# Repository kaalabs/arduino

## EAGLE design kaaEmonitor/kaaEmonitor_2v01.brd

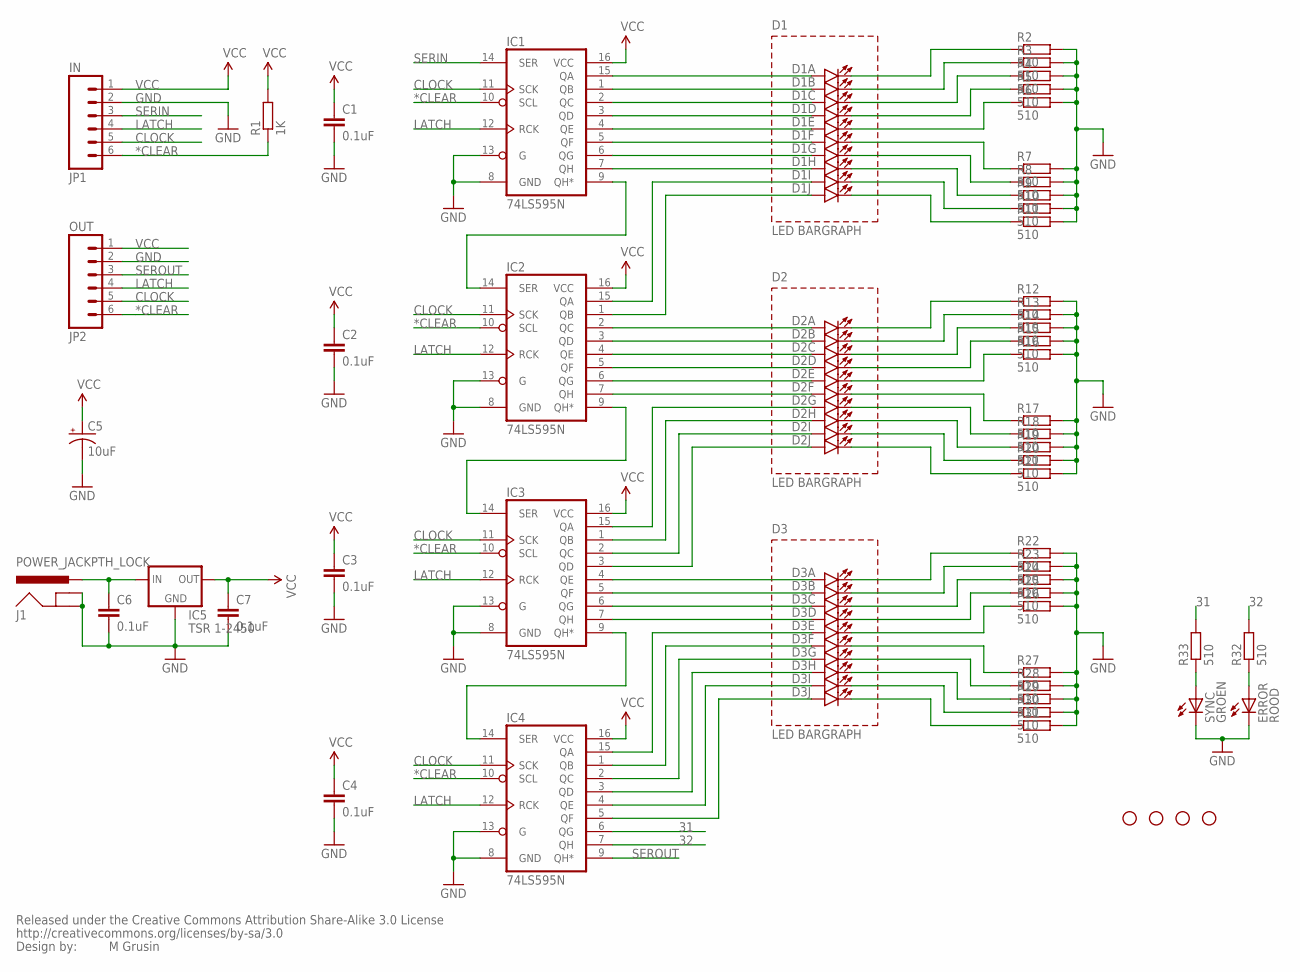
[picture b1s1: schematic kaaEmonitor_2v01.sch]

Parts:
C1, C2, C3, C4, C6, C7: 0.1uF; CAP-PTH-SMALL2
C5: 10uF; CPOL-RADIAL-10UF-25V
D1, D2, D3: LED_BARGRAPH_10; LED_BARGAPH_10
ERROR: ROOD; LED3MM
IC1, IC2, IC3, IC4: 74LS595N; DIL16
IC5: TSR 1-2450; TO220-IGO
J1: POWER_JACKPTH_LOCK; POWER_JACK_PTH_LOCK
JP1: IN; 1X06
JP2: OUT; 1X06
R1: 1K; 0204/5
R2, R3, R4, R5, R6, R7, R8, R9, R10, R11, R12, R13, R14, R15, R16, R17, R18, R19, R20, R21, R22, R23, R24, R25, R26, R27, R28, R29, R30, R31, R32, R33: 510; 0204/5
SO1, SO2, SO3, SO4: STAND-OFF
SYNC: GROEN; LED3MM
U$6: CREATIVE_COMMONS

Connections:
31: IC4.6 (QG), R33.2
32: IC4.7 (QH), R32.2
*CLEAR: IC1.10 (SCL), IC2.10 (SCL), IC3.10 (SCL), IC4.10 (SCL), JP1.6, JP2.6, R1.1
CLOCK: IC1.11 (SCK), IC2.11 (SCK), IC3.11 (SCK), IC4.11 (SCK), JP1.5, JP2.5
GND: C1.2, C2.2, C3.2, C4.2, C5.2 (-), C6.2, C7.2, ERROR.K (C), IC1.8 (GND), IC1.13 (G), IC2.8 (GND), IC2.13 (G), IC3.8 (GND), IC3.13 (G), IC4.8 (GND), IC4.13 (G), IC5.GND, J1.GND, J1.GNDBREAK, JP1.2, JP2.2, R2.2, R3.2, R4.2, R5.2, R6.2, R7.2, R8.2, R9.2, R10.2, R11.2, R12.2, R13.2, R14.2, R15.2, R16.2, R17.2, R18.2, R19.2, R20.2, R21.2, R22.2, R23.2, R24.2, R25.2, R26.2, R27.2, R28.2, R29.2, R30.2, R31.2, SYNC.K (C)
LATCH: IC1.12 (RCK), IC2.12 (RCK), IC3.12 (RCK), IC4.12 (RCK), JP1.4, JP2.4
unnamed: D1.1 (A), IC1.15 (QA)
unnamed: D1.2 (A), IC1.1 (QB)
unnamed: D1.3 (A), IC1.2 (QC)
unnamed: D1.4 (A), IC1.3 (QD)
unnamed: D1.5 (A), IC1.4 (QE)
unnamed: D1.6 (A), IC1.5 (QF)
unnamed: D1.7 (A), IC1.6 (QG)
unnamed: D1.8 (A), IC1.7 (QH)
unnamed: D1.9 (A), IC2.15 (QA)
unnamed: D1.10 (A), IC2.1 (QB)
unnamed: D2.8 (A), IC3.1 (QB)
unnamed: D2.7 (A), IC3.15 (QA)
unnamed: D2.9 (A), IC3.2 (QC)
unnamed: D2.10 (A), IC3.3 (QD)
unnamed: D3.1 (A), IC3.4 (QE)
unnamed: D3.2 (A), IC3.5 (QF)
unnamed: D3.3 (A), IC3.6 (QG)
unnamed: D3.4 (A), IC3.7 (QH)
unnamed: D2.1 (A), IC2.2 (QC)
unnamed: D2.2 (A), IC2.3 (QD)
unnamed: D2.3 (A), IC2.4 (QE)
unnamed: D2.4 (A), IC2.5 (QF)
unnamed: D2.5 (A), IC2.6 (QG)
unnamed: D2.6 (A), IC2.7 (QH)
unnamed: D1.20 (C), R2.1
unnamed: D1.19 (C), R3.1
unnamed: D3.5 (A), IC4.15 (QA)
unnamed: D3.6 (A), IC4.1 (QB)
unnamed: D1.18 (C), R4.1
unnamed: D1.17 (C), R5.1
unnamed: D1.16 (C), R6.1
unnamed: D1.15 (C), R7.1
unnamed: D1.14 (C), R8.1
unnamed: D1.13 (C), R9.1
unnamed: D1.12 (C), R10.1
unnamed: D1.11 (C), R11.1
unnamed: D2.20 (C), R12.1
unnamed: D2.19 (C), R13.1
unnamed: D3.7 (A), IC4.2 (QC)
unnamed: D3.8 (A), IC4.3 (QD)
unnamed: D3.9 (A), IC4.4 (QE)
unnamed: D3.10 (A), IC4.5 (QF)
unnamed: D2.18 (C), R14.1
unnamed: D2.17 (C), R15.1
unnamed: D2.16 (C), R16.1
unnamed: D2.15 (C), R17.1
unnamed: D2.14 (C), R18.1
unnamed: D2.13 (C), R19.1
unnamed: D2.12 (C), R20.1
unnamed: D2.11 (C), R21.1
unnamed: D3.20 (C), R22.1
unnamed: D3.19 (C), R23.1
unnamed: D3.18 (C), R24.1
unnamed: D3.17 (C), R25.1
unnamed: D3.16 (C), R26.1
unnamed: D3.15 (C), R27.1
unnamed: D3.14 (C), R28.1
unnamed: D3.13 (C), R29.1
unnamed: D3.12 (C), R30.1
unnamed: D3.11 (C), R31.1
unnamed: C6.1, IC5.IN, J1.PWR
unnamed: R33.1, SYNC.A
unnamed: ERROR.A, R32.1
unnamed: IC1.9 (QH*), IC2.14 (SER)
unnamed: IC2.9 (QH*), IC3.14 (SER)
unnamed: IC3.9 (QH*), IC4.14 (SER)
SERIN: IC1.14 (SER), JP1.3
SEROUT: IC4.9 (QH*), JP2.3
VCC: C1.1, C2.1, C3.1, C4.1, C5.1 (+), C7.1, IC1.16 (VCC), IC2.16 (VCC), IC3.16 (VCC), IC4.16 (VCC), IC5.OUT, JP1.1, JP2.1, R1.2

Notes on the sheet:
M Grusin
LED BARGRAPH

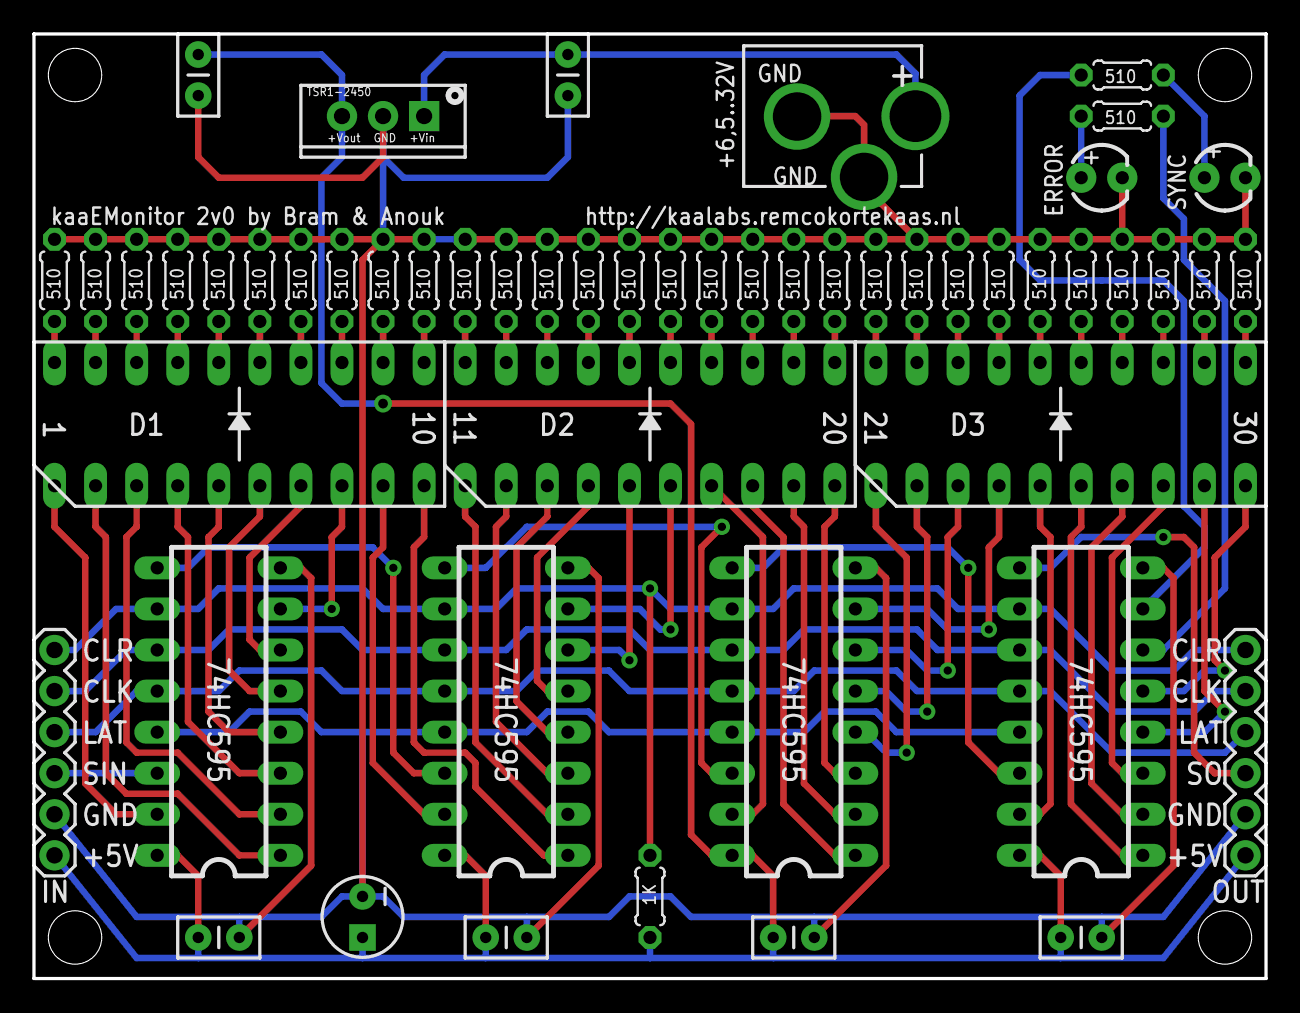
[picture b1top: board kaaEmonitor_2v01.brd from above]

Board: 2 copper layers, 76.2 x 58.4 mm, 58 parts (0 on the bottom side), 75 nets.

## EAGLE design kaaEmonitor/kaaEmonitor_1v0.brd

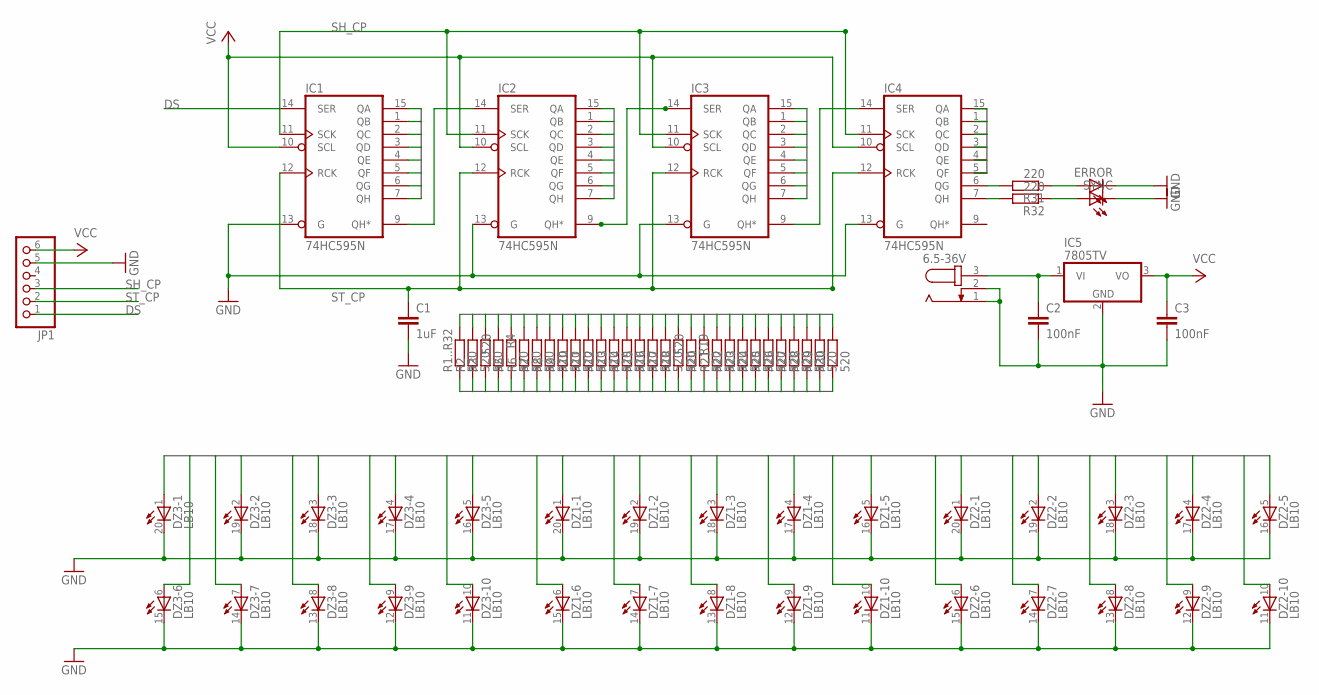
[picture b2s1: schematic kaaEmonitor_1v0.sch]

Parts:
6.5-36V: JACK-PLUG1; SPC4078
C1: 1uF; C025-025X050
C2, C3: 100nF; C025-024X044
DZ1, DZ2, DZ3: LB10
ERROR: LED3MM
IC1, IC2, IC3, IC4: 74HC595N; DIL16
IC5: 7805TV; TO220V
JP1: PINHD-1X6; 1X06
R1..R32, R2, R3, R4, R5, R6, R7, R8, R9, R10, R11, R12, R13, R14, R15, R16, R17, R18, R19, R20, R21, R22, R23, R24, R25, R26, R27, R28, R29, R30: 520; 0204/7
R31, R32: 220; 0204/7
SYNC: LED3MM

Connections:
DS: IC1.14 (SER), JP1.1
GND: 6.5-36V.1, 6.5-36V.2, C1.2, C2.2, C3.2, DZ1.11 (C), DZ1.12 (C), DZ1.13 (C), DZ1.14 (C), DZ1.15 (C), DZ1.16 (C), DZ1.17 (C), DZ1.18 (C), DZ1.19 (C), DZ1.20 (C), DZ2.11 (C), DZ2.12 (C), DZ2.13 (C), DZ2.14 (C), DZ2.15 (C), DZ2.16 (C), DZ2.17 (C), DZ2.18 (C), DZ2.19 (C), DZ2.20 (C), DZ3.11 (C), DZ3.12 (C), DZ3.13 (C), DZ3.14 (C), DZ3.15 (C), DZ3.16 (C), DZ3.17 (C), DZ3.18 (C), DZ3.19 (C), DZ3.20 (C), ERROR.K (C), IC1.8 (GND), IC1.13 (G), IC2.8 (GND), IC2.13 (G), IC3.8 (GND), IC3.13 (G), IC4.8 (GND), IC4.13 (G), IC5.2 (GND), JP1.5, SYNC.K (C)
LEDBUS1: DZ1.10 (A), R1..R32.1
LEDBUS2: DZ1.9 (A), R2.1
LEDBUS3: DZ1.8 (A), R3.1
LEDBUS4: DZ1.7 (A), R4.2
LEDBUS5: DZ1.6 (A), R5.1
LEDBUS6: DZ1.5 (A), R6.1
LEDBUS7: DZ1.4 (A), R7.1
LEDBUS8: DZ1.3 (A), R8.1
LEDBUS9: DZ1.2 (A), R9.1
LEDBUS10: DZ1.1 (A), R10.1
LEDBUS11: DZ2.10 (A), R11.1
LEDBUS12: DZ2.9 (A), R12.1
LEDBUS13: DZ2.8 (A), R13.1
LEDBUS14: DZ2.7 (A), R14.1
LEDBUS15: DZ2.6 (A), R15.1
LEDBUS16: DZ2.5 (A), R16.1
LEDBUS17: DZ2.4 (A), R17.1
LEDBUS18: DZ2.3 (A), R18.1
LEDBUS19: DZ2.2 (A), R19.2
LEDBUS20: DZ2.1 (A), R20.1
LEDBUS21: DZ3.10 (A), R21.1
LEDBUS22: DZ3.9 (A), R22.1
LEDBUS23: DZ3.8 (A), R23.1
LEDBUS24: DZ3.7 (A), R24.1
LEDBUS25: DZ3.6 (A), R25.1
LEDBUS26: DZ3.5 (A), R26.1
LEDBUS27: DZ3.4 (A), R27.1
LEDBUS28: DZ3.3 (A), R28.1
LEDBUS29: DZ3.2 (A), R29.1
LEDBUS30: DZ3.1 (A), R30.1
unnamed: IC1.9 (QH*), IC2.14 (SER)
unnamed: IC2.9 (QH*), IC3.14 (SER)
unnamed: IC3.9 (QH*), IC4.14 (SER)
unnamed: ERROR.A, R31.1
unnamed: R32.1, SYNC.A
unnamed: IC4.6 (QG), R31.2
unnamed: IC4.7 (QH), R32.2
unnamed: 6.5-36V.3, C2.1, IC5.1 (VI)
QBUS1: IC1.15 (QA), R1..R32.2
QBUS2: IC1.1 (QB), R2.2
QBUS3: IC1.2 (QC), R3.2
QBUS4: IC1.3 (QD), R4.1
QBUS5: IC1.4 (QE), R5.2
QBUS6: IC1.5 (QF), R6.2
QBUS7: IC1.6 (QG), R7.2
QBUS8: IC1.7 (QH), R8.2
QBUS9: IC2.15 (QA), R9.2
QBUS10: IC2.1 (QB), R10.2
QBUS11: IC2.2 (QC), R11.2
QBUS12: IC2.3 (QD), R12.2
QBUS13: IC2.4 (QE), R13.2
QBUS14: IC2.5 (QF), R14.2
QBUS15: IC2.6 (QG), R15.2
QBUS16: IC2.7 (QH), R16.2
QBUS17: IC3.15 (QA), R17.2
QBUS18: IC3.1 (QB), R18.2
QBUS19: IC3.2 (QC), R19.1
QBUS20: IC3.3 (QD), R20.2
QBUS21: IC3.4 (QE), R21.2
QBUS22: IC3.5 (QF), R22.2
QBUS23: IC3.6 (QG), R23.2
QBUS24: IC3.7 (QH), R24.2
QBUS25: IC4.15 (QA), R25.2
QBUS26: IC4.1 (QB), R26.2
QBUS27: IC4.2 (QC), R27.2
QBUS28: IC4.3 (QD), R28.2
QBUS29: IC4.4 (QE), R29.2
QBUS30: IC4.5 (QF), R30.2
SH_CP: IC1.11 (SCK), IC2.11 (SCK), IC3.11 (SCK), IC4.11 (SCK), JP1.3
ST_CP: C1.1, IC1.12 (RCK), IC2.12 (RCK), IC3.12 (RCK), IC4.12 (RCK), JP1.2
VCC: C3.1, IC1.10 (SCL), IC1.16 (VCC), IC2.10 (SCL), IC2.16 (VCC), IC3.10 (SCL), IC3.16 (VCC), IC4.10 (SCL), IC4.16 (VCC), IC5.3 (VO), JP1.6

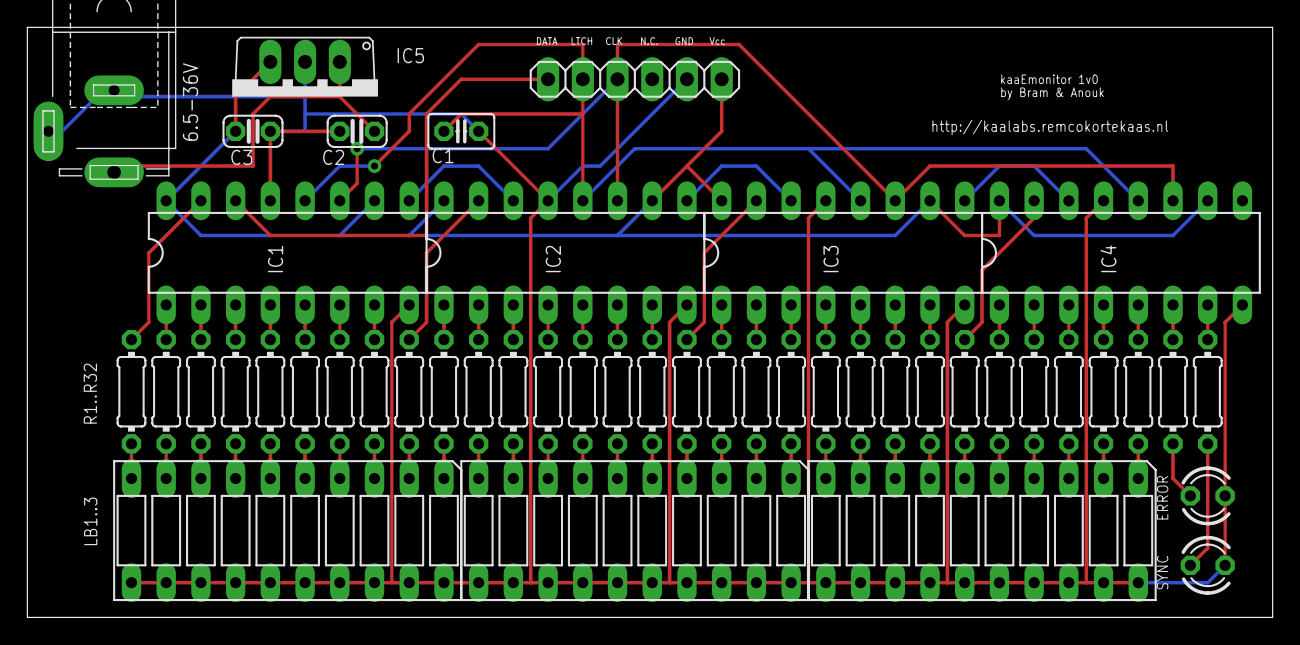
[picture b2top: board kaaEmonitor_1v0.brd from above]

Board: 2 copper layers, 91.1 x 43.2 mm, 47 parts (0 on the bottom side), 73 nets.

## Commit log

2014-09-14 Various adjustments
2015-08-20 Initial upload Arduino local

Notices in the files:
parts and their libraries:
SparkFun: Released under the Creative Commons Attribution Share-Alike 3.0 License
SparkFun: http://creativecommons.org/licenses/by-sa/3.0
SparkFun-PowerIC: Licensing: CC v3.0 Share-Alike You are welcome to use this library for commercial purposes.
